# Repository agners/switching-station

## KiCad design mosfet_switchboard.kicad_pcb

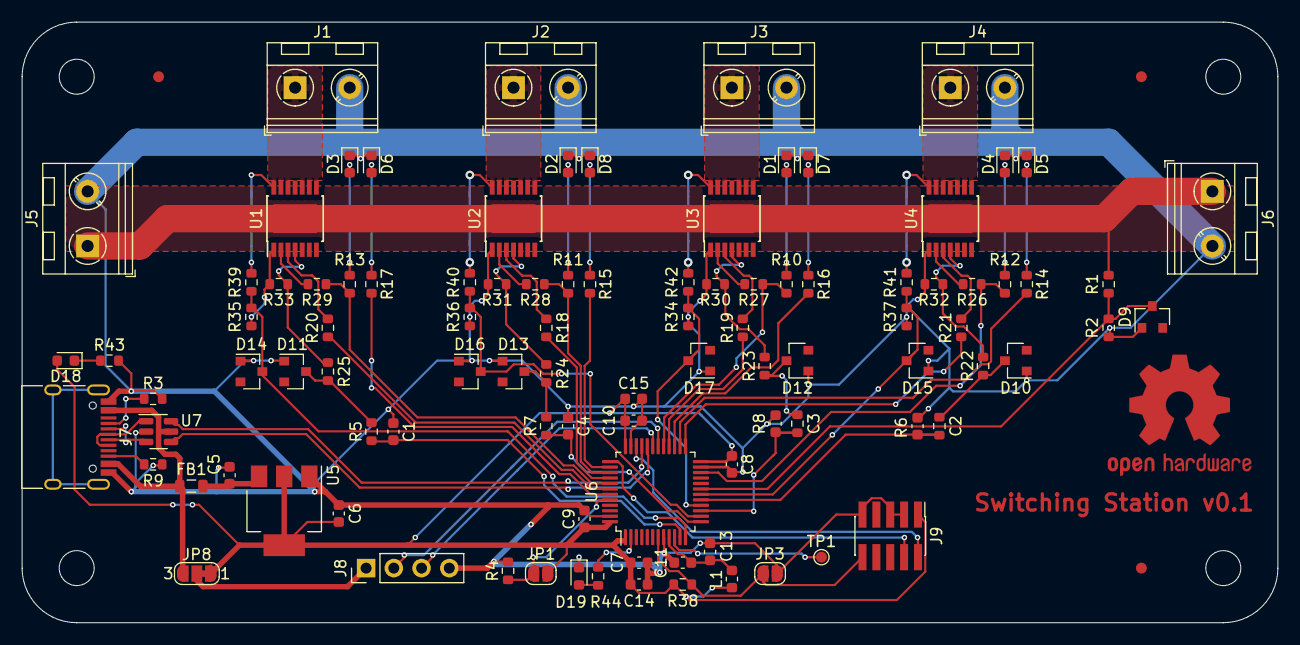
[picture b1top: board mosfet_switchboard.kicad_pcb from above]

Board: 2 copper layers, 115.0 x 55.0 mm, 99 parts (0 on the bottom side), 72 nets.

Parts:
C1, C2, C3, C4: 220pF; C_0603_1608Metric
C5, C6: 10µF; C_0603_1608Metric
C7, C8, C9, C10: 100nF; C_0603_1608Metric
C11: 10nF; C_0603_1608Metric
C13: 1µF; C_0603_1608Metric
C14, C15: 4.7µF; C_0603_1608Metric
D1, D2, D3, D4: GREEN; LED_0603_1608Metric
D5, D6, D7, D8: RED; LED_0603_1608Metric
D9, D10, D11, D12, D13, D14, D15, D16, D17: BZX84C3V3-T1; D_SOT-23_ANK
D18: BLUE; LED_0603_1608Metric
D19: PINK; LED_0603_1608Metric
FB1: 100Ohm @ 100MHz; L_0805_2012Metric
J1, J2, J3, J4: Power Output; TerminalBlock_RND_205-00045_1x02_P5.00mm_Horizontal
J5, J6: Power Input; TerminalBlock_RND_205-00045_1x02_P5.00mm_Horizontal
J7: USB_C_Receptacle_USB2.0; USB_C_Receptacle_HRO_TYPE-C-31-M-12
J8: Conn_01x04_Male; PinHeader_1x04_P2.54mm_Vertical
J9: Conn_ARM_JTAG_SWD_10; PinHeader_2x05_P1.27mm_Vertical_SMD
JP1, JP3: SolderJumper_2_Open; SolderJumper-2_P1.3mm_Open_RoundedPad1.0x1.5mm
JP8: SolderJumper_3_Bridged12; SolderJumper-3_P1.3mm_Bridged12_RoundedPad1.0x1.5mm_NumberL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
L1: 39nH; L_0603_1608Metric
R1, R39, R40, R41, R42: 12kΩ 1%; R_0603_1608Metric
R2, R34, R35, R36, R37: 1.8kΩ 1%; R_0603_1608Metric
R3, R9: 5.1kΩ 1%; R_0603_1608Metric
R4, R10, R11, R12, R13, R14, R15, R16, R17, R38, R43: 10kΩ; R_0603_1608Metric
R5, R6, R7, R8, R18, R19, R20, R21, R22, R23, R24, R25, R26, R27, R28, R29: 4.7kΩ; R_0603_1608Metric
R30, R31, R32, R33: 8.2kΩ 1%; R_0603_1608Metric
R44: 1kΩ; R_0603_1608Metric
TP1: TestPoint; TestPoint_Pad_D1.0mm
U1, U2, U3, U4: BTS7004-1EPP; Infineon_PG-TSDSO-14-22
U5: AMS1117-3.3; SOT-223-3_TabPin2
U6: STM32F042C4Tx; LQFP-48_7x7mm_P0.5mm
U7: USBLC6-2SC6; SOT-23-6

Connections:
+3.3VA: C11.1, C13.1, L1.2, U6.9 (VDDA)
+3V3: C6.1, C7.1, C8.1, C9.1, C10.1, C14.1, C15.1, D18.2 (A), J9.1 (VTref), JP1.2 (B), JP8.1 (A), L1.1, R38.2, U5.2 (VO), U6.1 (VBAT), U6.24 (VDD), U6.36 (VDDIO2), U6.48 (VDD)
+5V: FB1.1, J7.A4 (VBUS), J7.A9 (VBUS), J7.B4 (VBUS), J7.B9 (VBUS), JP8.3 (B), U7.5 (VBUS)
/Control/BOOT0: JP1.1 (A), R4.1, U6.44 (PF11)
/Control/NRST: J9.10 (~RESET~), JP3.1 (A), R38.1, U6.7 (NRST)
/Control/SWCLK: J9.4 (SWDCLK/TCK), U6.37 (PA14)
/Control/SWDIO: J9.2 (SWDIO/TMS), U6.34 (PA13)
/Control/UART_RX: J8.3, U6.31 (PA10)
/Control/UART_TX: J8.2, U6.30 (PA9)
/Control/USB_CC1: J7.A5 (CC1), R3.1
/Control/USB_CC2: J7.B5 (CC2), R9.1
/Control/USB_CONN_D+: J7.A6 (D+), J7.B6 (D+), U7.1 (I/O1)
/Control/USB_CONN_D-: J7.A7 (D-), J7.B7 (D-), U7.3 (I/O2)
/Control/USB_D+: U6.33 (PA12), U7.6 (I/O1)
/Control/USB_D-: U6.32 (PA11), U7.4 (I/O2)
/Power/Power Switch 1/VDD_SWITCHED: J1.1, R39.1, U1.8 (OUT), U1.9 (OUT), U1.10 (OUT), U1.12 (OUT), U1.13 (OUT), U1.14 (OUT)
/Power/Power Switch 2/VDD_SWITCHED: J2.1, R40.1, U2.8 (OUT), U2.9 (OUT), U2.10 (OUT), U2.12 (OUT), U2.13 (OUT), U2.14 (OUT)
/Power/Power Switch 3/VDD_SWITCHED: J3.1, R42.1, U3.8 (OUT), U3.9 (OUT), U3.10 (OUT), U3.12 (OUT), U3.13 (OUT), U3.14 (OUT)
/Power/Power Switch 4/VDD_SWITCHED: J4.1, R41.1, U4.8 (OUT), U4.9 (OUT), U4.10 (OUT), U4.12 (OUT), U4.13 (OUT), U4.14 (OUT)
GND: C1.1, C2.1, C3.1, C4.1, C5.2, C6.2, C7.2, C8.2, C9.2, C10.2, C11.2, C13.2, C14.2, C15.2, D1.1 (K), D2.1 (K), D3.1 (K), D4.1 (K), D5.1 (K), D6.1 (K), D7.1 (K), D8.1 (K), D9.2 (A), D10.2 (A), D11.2 (A), D12.2 (A), D13.2 (A), D14.2 (A), D15.2 (A), D16.2 (A), D17.2 (A), D19.1 (K), J1.2, J2.2, J3.2, J4.2, J5.2, J6.2, J7.A1 (GND), J7.A12 (GND), J7.B1 (GND), J7.B12 (GND), J8.4, J9.3 (GND), J9.5 (GND), J9.9 (GNDDetect), JP3.2 (B), R2.2, R3.2, R4.2, R9.2, R30.2, R31.2, R32.2, R33.2, R34.2, R35.2, R36.2, R37.2, R43.2, U1.1 (GND), U2.1 (GND), U3.1 (GND), U4.1 (GND), U5.1 (GND), U6.8 (VSSA), U6.23 (VSS), U6.35 (VSS), U6.47 (VSS), U7.2 (GND)
INPUT_ADC_U: D9.1 (K), R1.2, R2.1, U6.19 (PB1)
unnamed: C5.1, FB1.2, U5.3 (VI)
unnamed: D1.2 (A), R10.1
unnamed: D2.2 (A), R11.1
unnamed: D3.2 (A), R13.1
unnamed: D4.2 (A), R12.1
unnamed: D5.2 (A), R14.1
unnamed: D6.2 (A), R17.1
unnamed: D7.2 (A), R16.1
unnamed: D8.2 (A), R15.1
unnamed: D10.1 (K), R6.2, R22.1
unnamed: D11.1 (K), R5.2, R25.1
unnamed: D12.1 (K), R8.2, R23.1
unnamed: D13.1 (K), R7.2, R24.1
unnamed: D18.1 (K), R43.1
unnamed: D19.2 (A), R44.2
unnamed: J8.1, JP8.2 (C)
unnamed: R18.2, U2.3 (DEN)
unnamed: R19.2, U3.3 (DEN)
unnamed: R20.2, U1.3 (DEN)
unnamed: R21.2, U4.3 (DEN)
unnamed: R22.2, R32.1, U4.4 (IS)
unnamed: R23.2, R30.1, U3.4 (IS)
unnamed: R24.2, R31.1, U2.4 (IS)
unnamed: R25.2, R33.1, U1.4 (IS)
unnamed: R26.2, U4.2 (IN)
unnamed: R27.2, U3.2 (IN)
unnamed: R28.2, U2.2 (IN)
unnamed: R29.2, U1.2 (IN)
unnamed: R44.1, U6.2 (PC13)
unnamed: TP1.1, U6.10 (PA0)
SW1_ADC_I: C1.2, R5.1, U6.11 (PA1)
SW1_ADC_U: D14.1 (K), R35.1, R39.2, U6.12 (PA2)
SW1_DEN: R20.1, U6.42 (PB6)
SW1_FAULT: R17.2, U6.43 (PB7)
SW1_IN: R13.2, R29.1, U6.41 (PB5)
SW2_ADC_I: C4.2, R7.1, U6.13 (PA3)
SW2_ADC_U: D16.1 (K), R36.1, R40.2, U6.14 (PA4)
SW2_DEN: R18.1, U6.40 (PB4)
SW2_FAULT: R15.2, U6.38 (PA15)
SW2_IN: R11.2, R28.1, U6.39 (PB3)
SW3_ADC_I: C3.2, R8.1, U6.15 (PA5)
SW3_ADC_U: D17.1 (K), R34.1, R42.2, U6.16 (PA6)
SW3_DEN: R19.1, U6.28 (PB15)
SW3_FAULT: R16.2, U6.27 (PB14)
SW3_IN: R10.2, R27.1, U6.29 (PA8)
SW4_ADC_I: C2.2, R6.1, U6.17 (PA7)
SW4_ADC_U: D15.1 (K), R37.1, R41.2, U6.18 (PB0)
SW4_DEN: R21.1, U6.25 (PB12)
SW4_FAULT: R14.2, U6.26 (PB13)
SW4_IN: R12.2, R26.1, U6.22 (PB11)
VDD: J5.1, J6.1, R1.1, U1.15 (VS), U2.15 (VS), U3.15 (VS), U4.15 (VS)

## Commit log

2020-10-25 initial design/P-channel MOSFETs
2020-10-25 initial version with STM32, before splitup
2020-10-25 split into multiple sheets
2020-10-25 use USB-C and add analog filtering
2020-10-26 complete current sense circuit, add leds
2020-10-26 fix LEDs, add power LED
2020-11-07 add voltage measurement
2020-11-07 introduce hierarchical sheets for power switches
2020-11-08 initial component placement
2020-11-08 updated footprints, adjustments in placement
2020-11-08 place decoupling capacitors nicer, add USB ESD protection
2020-11-09 layouting finished, some microcontroller connection rearrangements
2020-11-09 use 1% resistor for voltage divider, add one more fiducial
2020-11-09 add uC controlled status LED, improve filling zones, move LED closer to connectors
